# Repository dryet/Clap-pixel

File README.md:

## Neopixel based light
This repository contains PCB design files, 3D printable cover and code for neopixel based light which turns ON and OFF on two claps.
The PCB was manufactured at JLCPCB.com and the cover was printed using transluscent PLA filament.
STM32CubeMX can be used to modifi the `.ioc` file which generates basic structure for the STM32G0 codebase. Code compilation is done using the STM32CubeCLT.

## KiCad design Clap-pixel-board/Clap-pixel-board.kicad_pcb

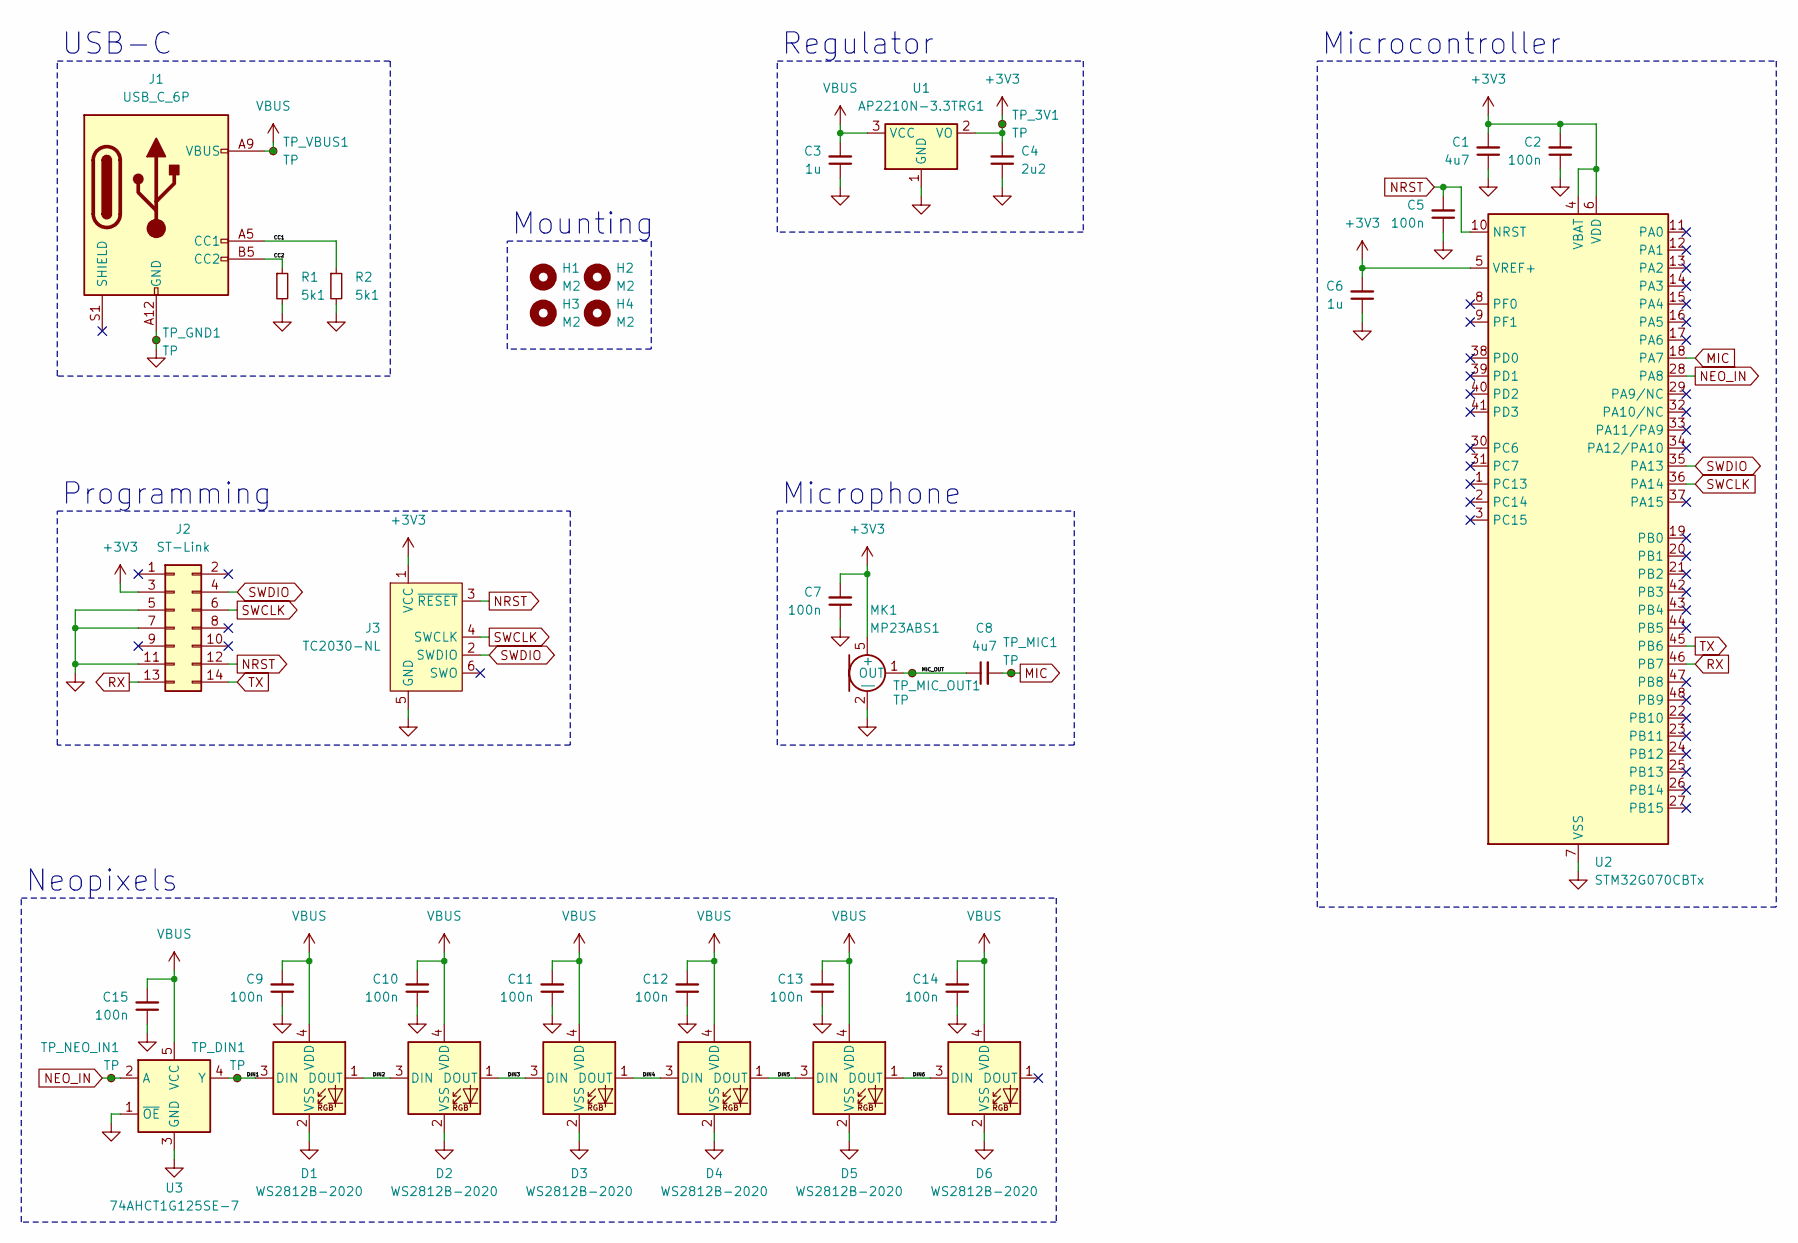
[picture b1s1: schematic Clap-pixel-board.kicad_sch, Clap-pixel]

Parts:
C1, C8: 4u7; C_0603_1608Metric
C2, C5, C7, C9, C10, C11, C12, C13, C14, C15: 100n; C_0402_1005Metric
C3, C6: 1u; C_0402_1005Metric
C4: 2u2; C_0603_1608Metric
D1, D2, D3, D4, D5, D6: WS2812B-2020; LED_WS2812B-2020_PLCC4_2.0x2.0mm
H1, H2, H3, H4: M2; MountingHole_2.2mm_M2
J1: USB_C_6P; USB_C_Receptacle_GCT_USB4125-xx-x-0190_6P_TopMnt_Horizontal
J2: ST-Link; PinHeader_2x07_P1.27mm_Vertical_SMD
J3: TC2030-NL; Tag-Connect_TC2030-IDC-NL_2x03_P1.27mm_Vertical
MK1: MP23ABS1; MIC_MP23ABS1TR
R1, R2: 5k1; R_0402_1005Metric
TP_3V1: TP; TestPoint_Keystone_5019_Minature
TP_DIN1: TP; TestPoint_Keystone_5019_Minature
TP_GND1: TP; TestPoint_Keystone_5015_Micro-Minature
TP_MIC1: TP; TestPoint_Keystone_5015_Micro-Minature
TP_MIC_OUT1: TP; TestPoint_Keystone_5015_Micro-Minature
TP_NEO_IN1: TP; TestPoint_Keystone_5019_Minature
TP_VBUS1: TP; TestPoint_Keystone_5015_Micro-Minature
U1: AP2210N-3.3TRG1; SOT-23-3
U2: STM32G070CBTx; LQFP-48_7x7mm_P0.5mm
U3: 74AHCT1G125SE-7; SOT-353_SC-70-5

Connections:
+3V3: C1.2, C2.2, C4.2, C6.2, C7.2, J2.3, J3.1 (VCC), MK1.5 (+), TP_3V1.1, U1.2 (VO), U2.4 (VBAT), U2.5 (VREF+), U2.6 (VDD)
/CC1: J1.A5 (CC1), R2.1
/CC2: J1.B5 (CC2), R1.1
/DIN1: D1.3 (DIN), TP_DIN1.1, U3.4 (Y)
/DIN2: D1.1 (DOUT), D2.3 (DIN)
/DIN3: D2.1 (DOUT), D3.3 (DIN)
/DIN4: D3.1 (DOUT), D4.3 (DIN)
/DIN5: D4.1 (DOUT), D5.3 (DIN)
/DIN6: D5.1 (DOUT), D6.3 (DIN)
/MIC_OUT: C8.1, MK1.1 (OUT), TP_MIC_OUT1.1
GND: C1.1, C2.1, C3.1, C4.1, C5.1, C6.1, C7.1, C9.1, C10.1, C11.1, C12.1, C13.1, C14.1, C15.1, D1.2 (VSS), D2.2 (VSS), D3.2 (VSS), D4.2 (VSS), D5.2 (VSS), D6.2 (VSS), J1.A12 (GND), J1.B12 (GND), J2.5, J2.7, J2.11, J3.5 (GND), MK1.2 (|), MK1.3 (-), MK1.4 (-), R1.2, R2.2, TP_GND1.1, U1.1 (GND), U2.7 (VSS), U3.1 (~OE), U3.3 (GND)
MIC: C8.2, TP_MIC1.1, U2.18 (PA7)
NEO_IN: TP_NEO_IN1.1, U2.28 (PA8), U3.2 (A)
NRST: C5.2, J2.12, J3.3 (~RESET), U2.10 (NRST)
RX: J2.13, U2.46 (PB7)
SWCLK: J2.6, J3.4 (SWCLK), U2.36 (PA14)
SWDIO: J2.4, J3.2 (SWDIO), U2.35 (PA13)
TX: J2.14, U2.45 (PB6)
VBUS: C3.2, C9.2, C10.2, C11.2, C12.2, C13.2, C14.2, C15.2, D1.4 (VDD), D2.4 (VDD), D3.4 (VDD), D4.4 (VDD), D5.4 (VDD), D6.4 (VDD), J1.A9 (VBUS), J1.B9 (VBUS), TP_VBUS1.1, U1.3 (VCC), U3.5 (VCC)

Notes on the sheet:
Mounting
Microphone
Neopixels
Microcontroller
Programming
Regulator
USB-C

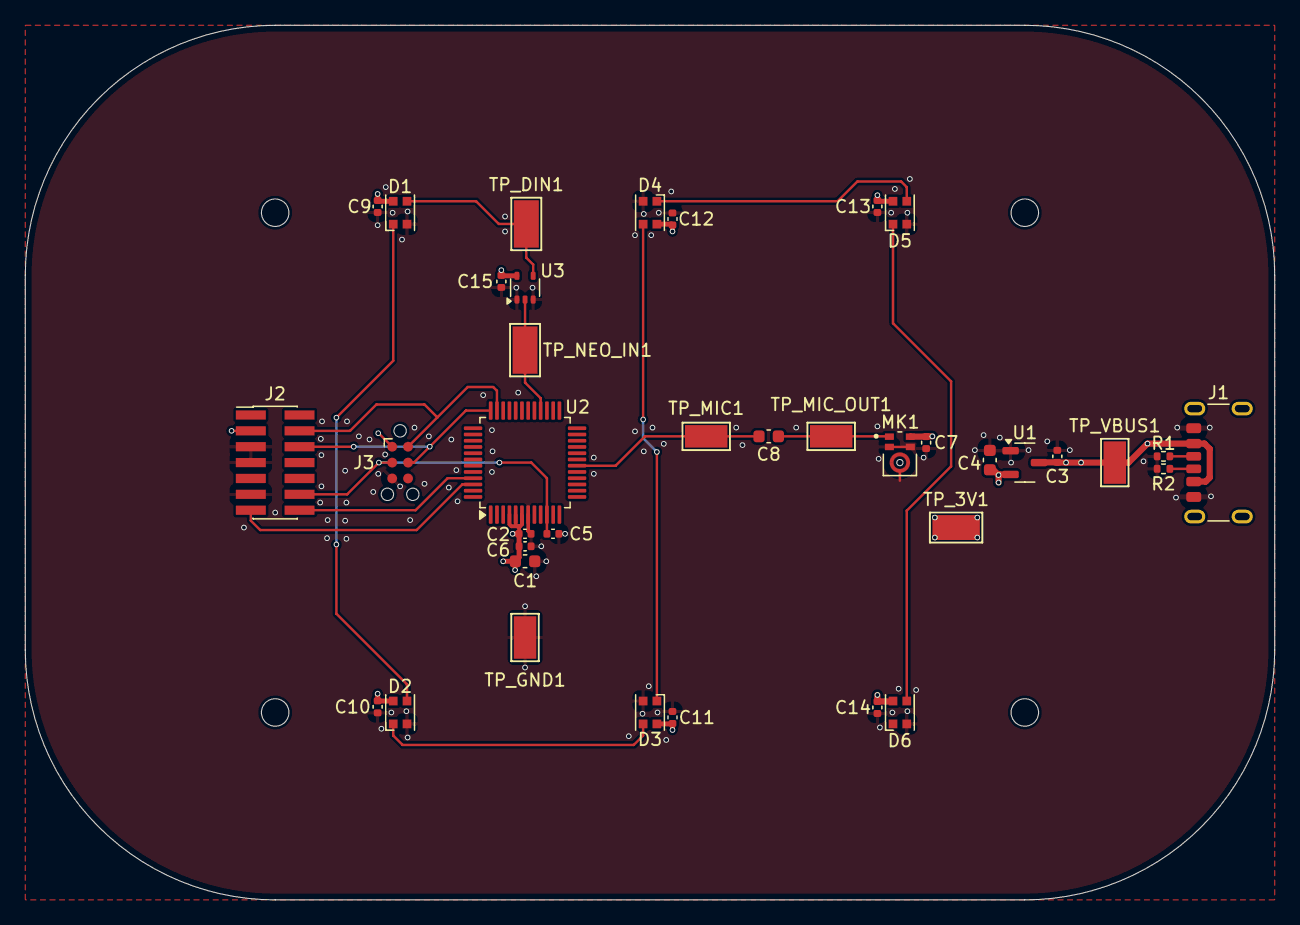
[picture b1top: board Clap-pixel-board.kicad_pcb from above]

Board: 4 copper layers, 100.0 x 70.0 mm, 41 parts (0 on the bottom side), 19 nets.

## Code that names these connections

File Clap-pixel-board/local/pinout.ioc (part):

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Mcu.Name=STM32G070CBTx
Mcu.Package=LQFP48
Mcu.UserName=STM32G070CBTx
PA13.Mode=Serial_Wire
PA13.Signal=SYS_SWDIO
PA14-BOOT0.Mode=Serial_Wire
PA14-BOOT0.Signal=SYS_SWCLK
PA7.Mode=IN7
PA7.Signal=ADC1_IN7
PA8.Signal=S_TIM1_CH1
PB6.Mode=Asynchronous
PB6.Signal=USART1_TX
PB7.Mode=Asynchronous
PB7.Signal=USART1_RX
RCC.HSE_VALUE=8000000
RCC.SYSCLKFreq_VALUE=64000000
RCC.SYSCLKSource=RCC_SYSCLKSOURCE_PLLCLK
board=custom

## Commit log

2025-01-09 Added KiCAD project
2025-01-09 Create local folder
2025-01-17 Schematic finished
2025-01-29 Finished PCB
2025-01-29 Add 3D files
2025-03-17 Lights work now
2025-03-20 It works on claps
2025-04-30 Refactor
2025-04-30 Apply gitignore
